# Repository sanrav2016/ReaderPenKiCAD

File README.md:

# ReaderPen KiCAD

KiCAD files for Reader Pen project. Manufacturing files for the PCB can be found here: https://github.com/sanrav2016/ReaderPenPCB.

Image of the schematic:

Some notes:
- We are using the STM32H723 microcontroller. STM is a reputable microcontroller manufacturer that dominates the commercial embedded systems market. This particular model belongs to their high-performance MCU series. The STM32H723 has a Cortex M7, and the VET6 package can run at 550MHz with 1 M flash and 564 K RAM. We have included an external 50 MHz clock. 
- We are using the TP4056 for microUSB charge control for a 3.7V 1000mAh LiPo battery.
- RGB LED for status indication
- Scan LEDs to highlight paper when reading
- The camera module in this system is the Himax HM01B0. It will not be ordered as we already have it at home from the Arducam module. A 2.8V LDO is necessarily included. 
- SWD for programming
- TRRS audio jack for speaker and mic (ADC/DAC). For simplicity no DSP is implemented.

The system will be programmed through STM32CubeIDE. Currently we are planning on using the C distributions of Tesseract and espeak, while implementing manual image processing. A demo of this concept can be found here: https://github.com/sanrav2016/ReaderPenRPiDemo.

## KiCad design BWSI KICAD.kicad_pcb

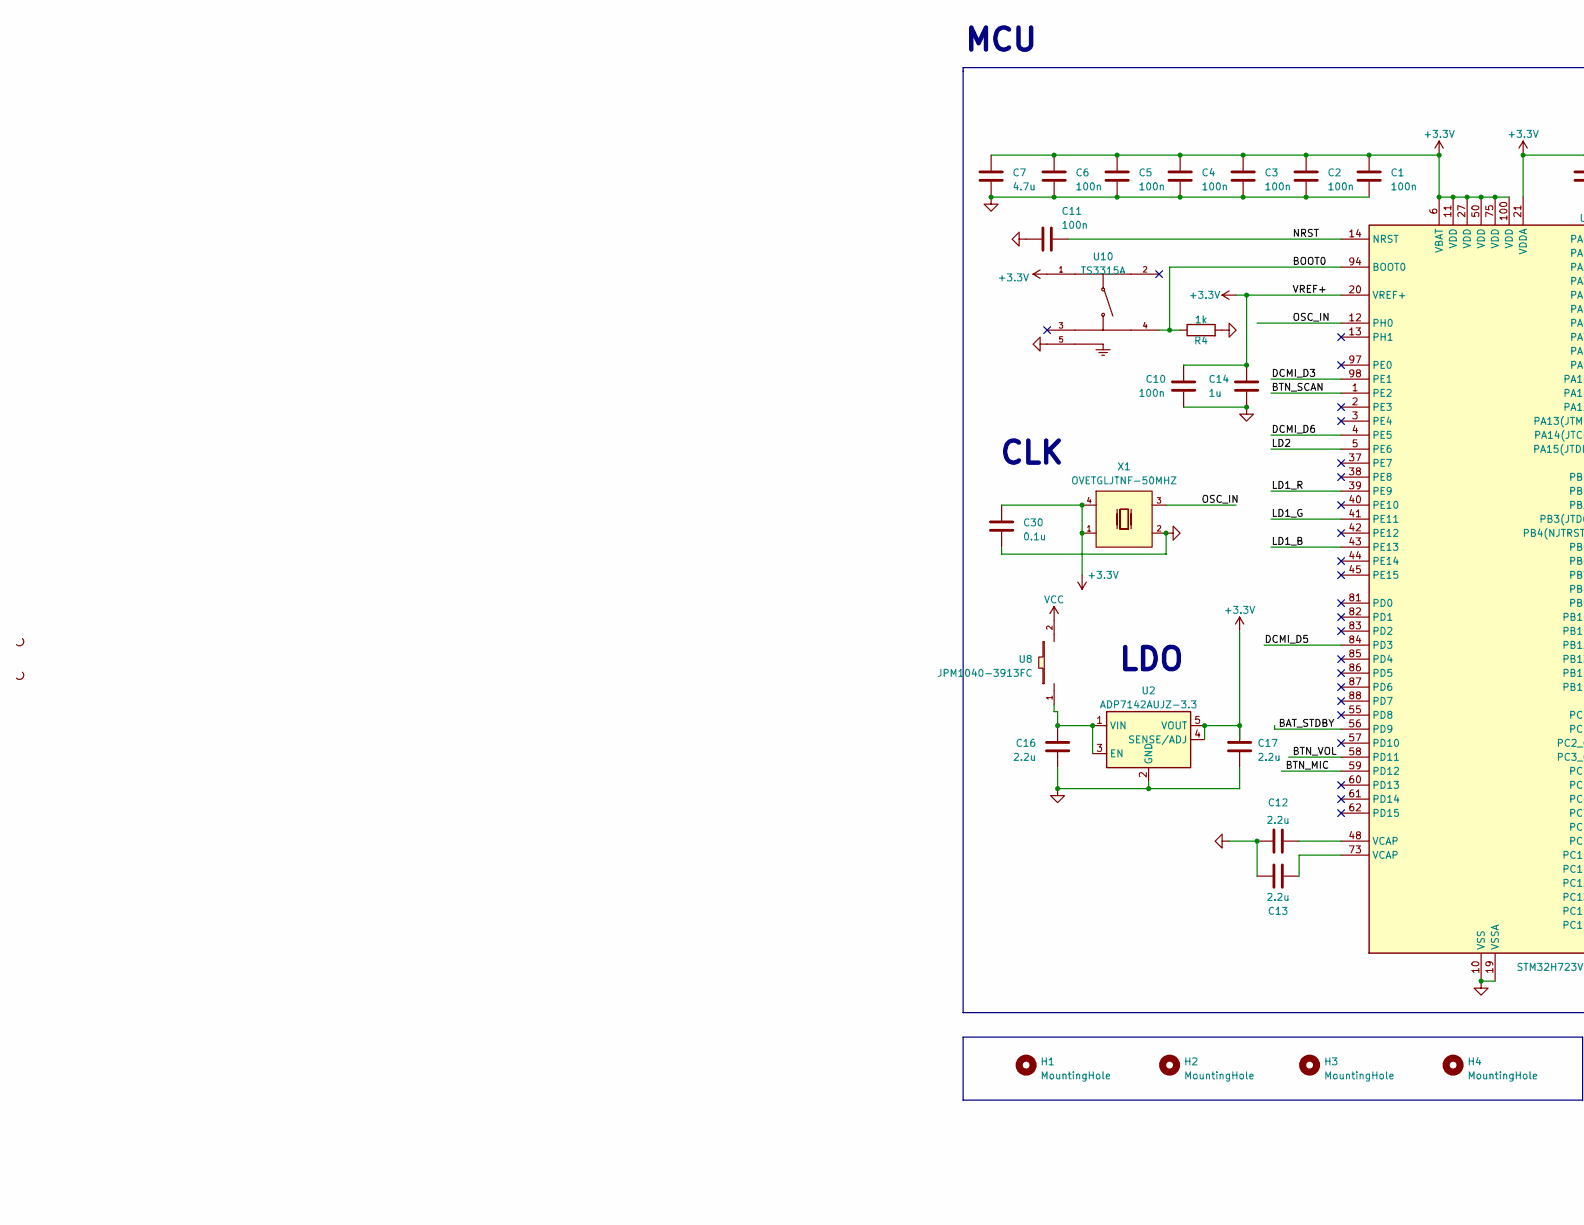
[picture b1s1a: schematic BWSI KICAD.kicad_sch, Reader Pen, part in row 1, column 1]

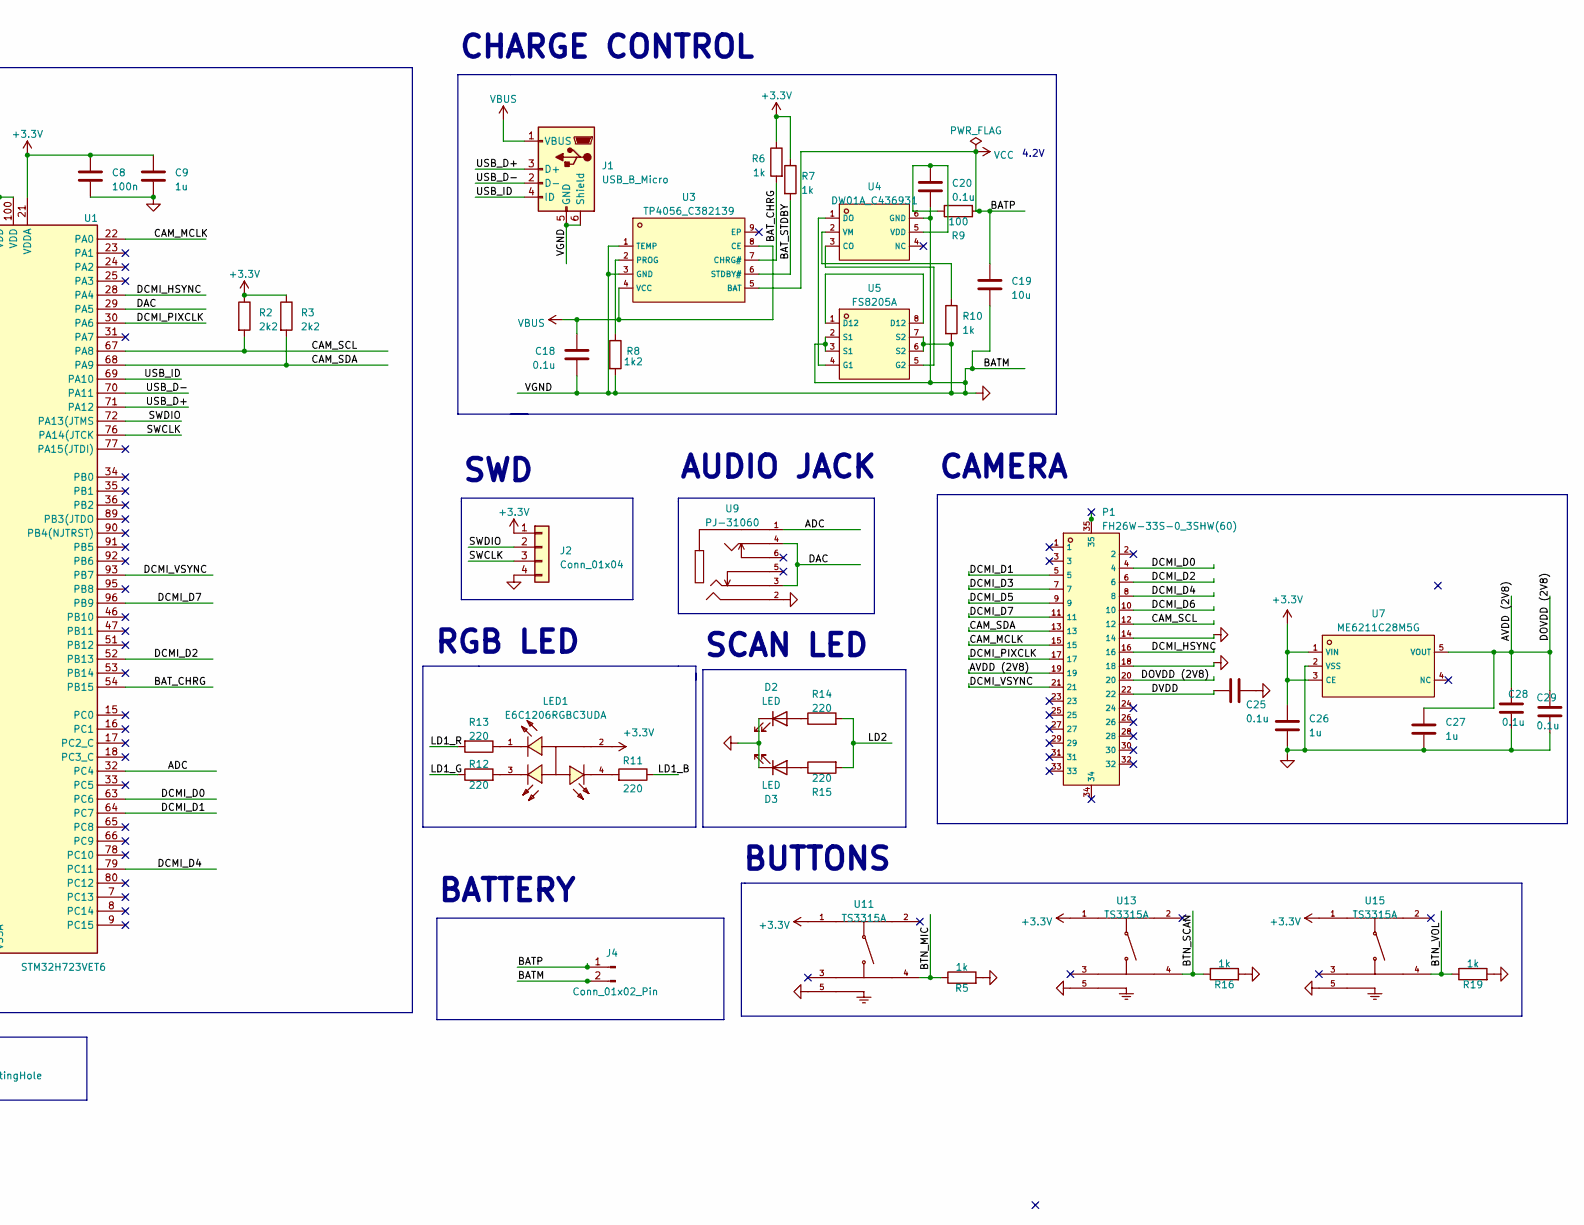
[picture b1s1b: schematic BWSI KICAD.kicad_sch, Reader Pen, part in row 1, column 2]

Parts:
C1, C2, C3, C4, C5, C6, C8, C10, C11: 100n; C_0402_1005Metric
C7: 4.7u; C_0402_1005Metric
C9, C14, C26, C27: 1u; C_0402_1005Metric
C12, C13, C16, C17: 2.2u; C_0402_1005Metric
C18, C20, C25, C28, C29, C30: 0.1u; C_0402_1005Metric
C19: 10u; C_0402_1005Metric
D2, D3: LED; LED_0805_2012Metric
H1, H2, H3, H4: MountingHole; MountingHole_2.2mm_M2
J1: USB_B_Micro; USB_Micro-B_Molex_47346-0001
J2: Conn_01x04; SolderWire-0.25sqmm_1x04_P4.2mm_D0.65mm_OD1.7mm
J4: Conn_01x02_Pin; SolderWire-0.25sqmm_1x02_P4.2mm_D0.65mm_OD1.7mm
LED1: E6C1206RGBC3UDA; LED-SMD_4P-L3.0-W1.5-TL-FD; LCSC C375571
P1: FH26W-33S-0_3SHW(60); FPC-SMD_FH26W-33S-0.3SHW-60; LCSC C424654
R2, R3: 2k2; R_0402_1005Metric
R4, R5, R6, R7, R10, R16, R19: 1k; R_0402_1005Metric
R8: 1k2; R_0402_1005Metric
R9: 100; R_0402_1005Metric
R11, R12, R13, R14, R15: 220; R_0402_1005Metric
U1: STM32H723VET6; LQFP-100_14x14mm_P0.5mm
U2: ADP7142AUJZ-3.3; TSOT-23-5
U3: TP4056_C382139; ESOP-8_L4.9-W3.9-P1.27-LS6.0-BL-EP; LCSC C382139
U4: DW01A_C436931; SOT-23-6_L2.9-W1.6-P0.95-LS2.8-BL; LCSC C436931
U5: FS8205A; TSSOP-8_L4.4-W3.0-P0.65-LS6.4-BL-2; LCSC C16052
U7: ME6211C28M5G; SOT-23-5_L3.0-W1.7-P0.95-LS2.8-BR; LCSC C53099
U8: JPM1040-3913FC; SW-SMD_SMK_JPM1040-XXXXFC; LCSC C516063
U9: PJ-31060; AUDIO-SMD_HOOYA_PJ-31060; LCSC C2939583
U10, U11, U13, U15: TS3315A; SW-SMD_4P-L3.4-W3.4-P2.00-LS4.0_TS3315A160GF; LCSC C412367
X1: OVETGLJTNF-50MHZ; OSC-SMD_4P-L5.0-W3.2-BL_SG5032; LCSC C117891

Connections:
+3.3V: C1.1, C2.1, C3.1, C4.1, C5.1, C6.1, C7.1, C8.1, C9.1, C10.1, C14.1, C17.1, C26.1, C30.1, J2.1, LED1.2 (+), R2.1, R3.1, R6.1, R7.1, U1.6 (VBAT), U1.11 (VDD), U1.20 (VREF+), U1.21 (VDDA), U1.27 (VDD), U1.50 (VDD), U1.75 (VDD), U1.100 (VDD), U2.4 (SENSE/ADJ), U2.5 (VOUT), U7.1 (VIN), U7.3 (CE), U10.1 (A), U11.1 (A), U13.1 (A), U15.1 (A), X1.1 (tri), X1.4 (VCC)
/ADC: U1.32 (PC4), U9.1
/AVDD (2V8): C27.1, C28.1, C29.2, P1.19, P1.20, U7.5 (VOUT)
/BAT_CHRG: R6.2, U1.54 (PB15), U3.7 (CHRG#)
/BAT_STDBY: R7.2, U1.56 (PD9), U3.6 (STDBY#)
/BOOT0: R4.1, U1.94 (BOOT0), U10.4 (D)
/BTN_MIC: R5.1, U1.59 (PD12), U11.4 (D)
/BTN_SCAN: R16.1, U1.1 (PE2), U13.4 (D)
/BTN_VOL: R19.1, U1.58 (PD11), U15.4 (D)
/CAM_MCLK: P1.15, U1.22 (PA0)
/CAM_SCL: P1.12, R2.2, U1.67 (PA8)
/CAM_SDA: P1.13, R3.2, U1.68 (PA9)
/DAC: U1.29 (PA5), U9.3, U9.4
/DCMI_D0: P1.4, U1.63 (PC6)
/DCMI_D1: P1.5, U1.64 (PC7)
/DCMI_D2: P1.6, U1.52 (PB13)
/DCMI_D3: P1.7, U1.98 (PE1)
/DCMI_D4: P1.8, U1.79 (PC11)
/DCMI_D5: P1.9, U1.84 (PD3)
/DCMI_D6: P1.10, U1.4 (PE5)
/DCMI_D7: P1.11, U1.96 (PB9)
/DCMI_HSYNC: P1.16, U1.28 (PA4)
/DCMI_PIXCLK: P1.17, U1.30 (PA6)
/DCMI_VSYNC: P1.21, U1.93 (PB7)
/DVDD: C25.2, P1.22
/LD1_B: R11.1, U1.43 (PE13)
/LD1_G: R12.1, U1.41 (PE11)
/LD1_R: R13.2, U1.39 (PE9)
/LD2: R14.2, R15.2, U1.5 (PE6)
/NRST: C11.1, U1.14 (NRST)
/OSC_IN: U1.12 (PH0), X1.3 (OUT)
/SWCLK: J2.3, U1.76 (PA14(JTCK)
/SWDIO: J2.2, U1.72 (PA13(JTMS)
/USB_D+: J1.3 (D+), U1.71 (PA12)
/USB_D-: J1.2 (D-), U1.70 (PA11)
/USB_ID: J1.4 (ID), U1.69 (PA10)
GND: C1.2, C2.2, C3.2, C4.2, C5.2, C6.2, C7.2, C8.2, C9.2, C10.2, C11.2, C12.1, C13.1, C14.2, C16.2, C17.2, C18.2, C19.2, C20.2, C25.1, C26.2, C27.2, C28.2, C29.1, C30.2, D2.1 (K), D3.1 (K), J1.5 (GND), J1.6 (Shield), J2.4, J4.2, P1.14, P1.18, R4.2, R5.2, R8.2, R10.2, R16.2, R19.2, U1.10 (VSS), U1.19 (VSSA), U1.26 (VSS), U1.49 (VSS), U1.74 (VSS), U1.99 (VSS), U2.2 (GND), U3.1 (TEMP), U3.3 (GND), U4.6 (GND), U5.2 (S1), U5.3 (S1), U5.6 (S2), U5.7 (S2), U7.2 (VSS), U9.2, U10.5 (GND), U11.5 (GND), U13.5 (GND), U15.5 (GND), X1.2 (GND)
unnamed: C12.2, U1.48 (VCAP)
unnamed: C13.2, U1.73 (VCAP)
unnamed: D2.2 (A), R14.1
unnamed: D3.2 (A), R15.1
unnamed: LED1.1 (-), R13.1
unnamed: LED1.3 (-), R12.2
unnamed: LED1.4 (-), R11.2
unnamed: C16.1, U2.1 (VIN), U2.3 (EN), U8.1
unnamed: R8.1, U3.2 (PROG)
unnamed: U4.3 (CO), U5.5 (G2)
unnamed: U4.1 (DO), U5.4 (G1)
unnamed: C20.1, R9.1, U4.5 (VDD)
unnamed: R10.1, U4.2 (VM)
unnamed: U5.1 (D12), U5.8 (D12)
VBUS: C18.1, J1.1 (VBUS), U3.4 (VCC), U3.8 (CE)
VCC: C19.1, J4.1, R9.2, U3.5 (BAT), U8.2

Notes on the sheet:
CAMERA
SCAN LED
AUDIO JACK
LDO
BUTTONS
CHARGE CONTROL
RGB LED
4.2V
CLK
SWD
BATTERY
MCU

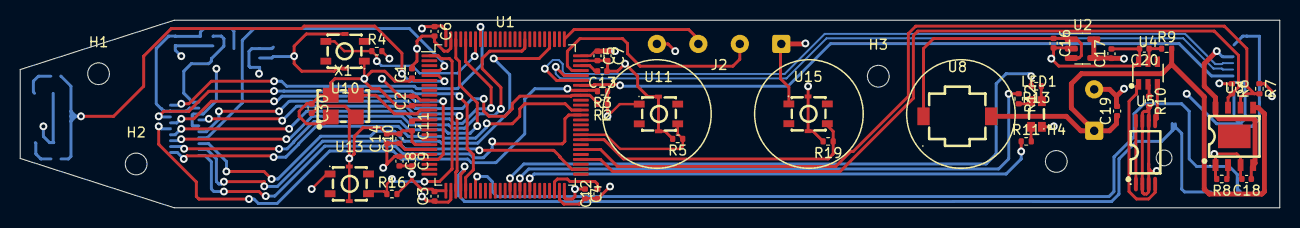
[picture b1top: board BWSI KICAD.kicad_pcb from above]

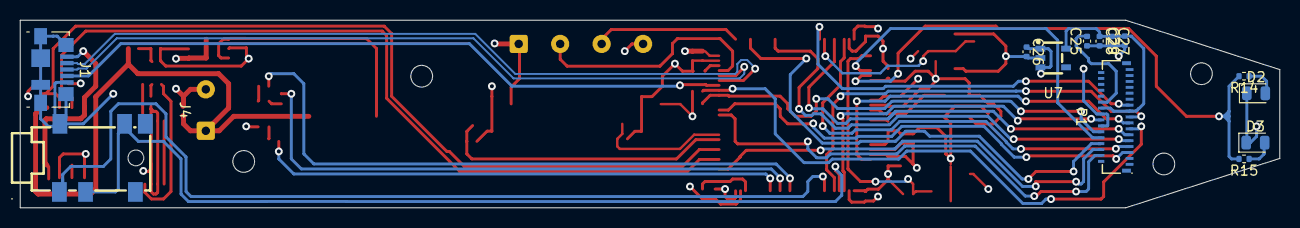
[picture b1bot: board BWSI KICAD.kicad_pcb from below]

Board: 4 copper layers, 127.6 x 19.0 mm, 65 parts (14 on the bottom side), 53 nets.
